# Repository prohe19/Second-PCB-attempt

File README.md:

# Second-PCB-attempt

well here we go my second attempt of creating PCB of mechanical keyboard

I supposed we'll call it a numpad board? well because it only consists of 17 MX only hotswap switches (finally using matrix yeay!!)

this time on my second attempt I tried to include a rotary encoder so that you use to control volume on your pc, scroll up or down and many more!
also I included an 9.1 OLED LCD display why? I believe the right term to desribe it is just for "fun" :D
well you can use the LCD display to display the capslock on or just to display silly small pictures on your numpad board.

This version is still not fixed, might change more in the future because Im still not happy with the componen placements.
Again, my priority is AESTHETIC of the PCB sooo it takes me such a loonnggggggg time to design this.

Pros

-HOTSWAPABLE!!!!!!

-rotary encoder

-OLED LCD display

Cons

-no RGB :(

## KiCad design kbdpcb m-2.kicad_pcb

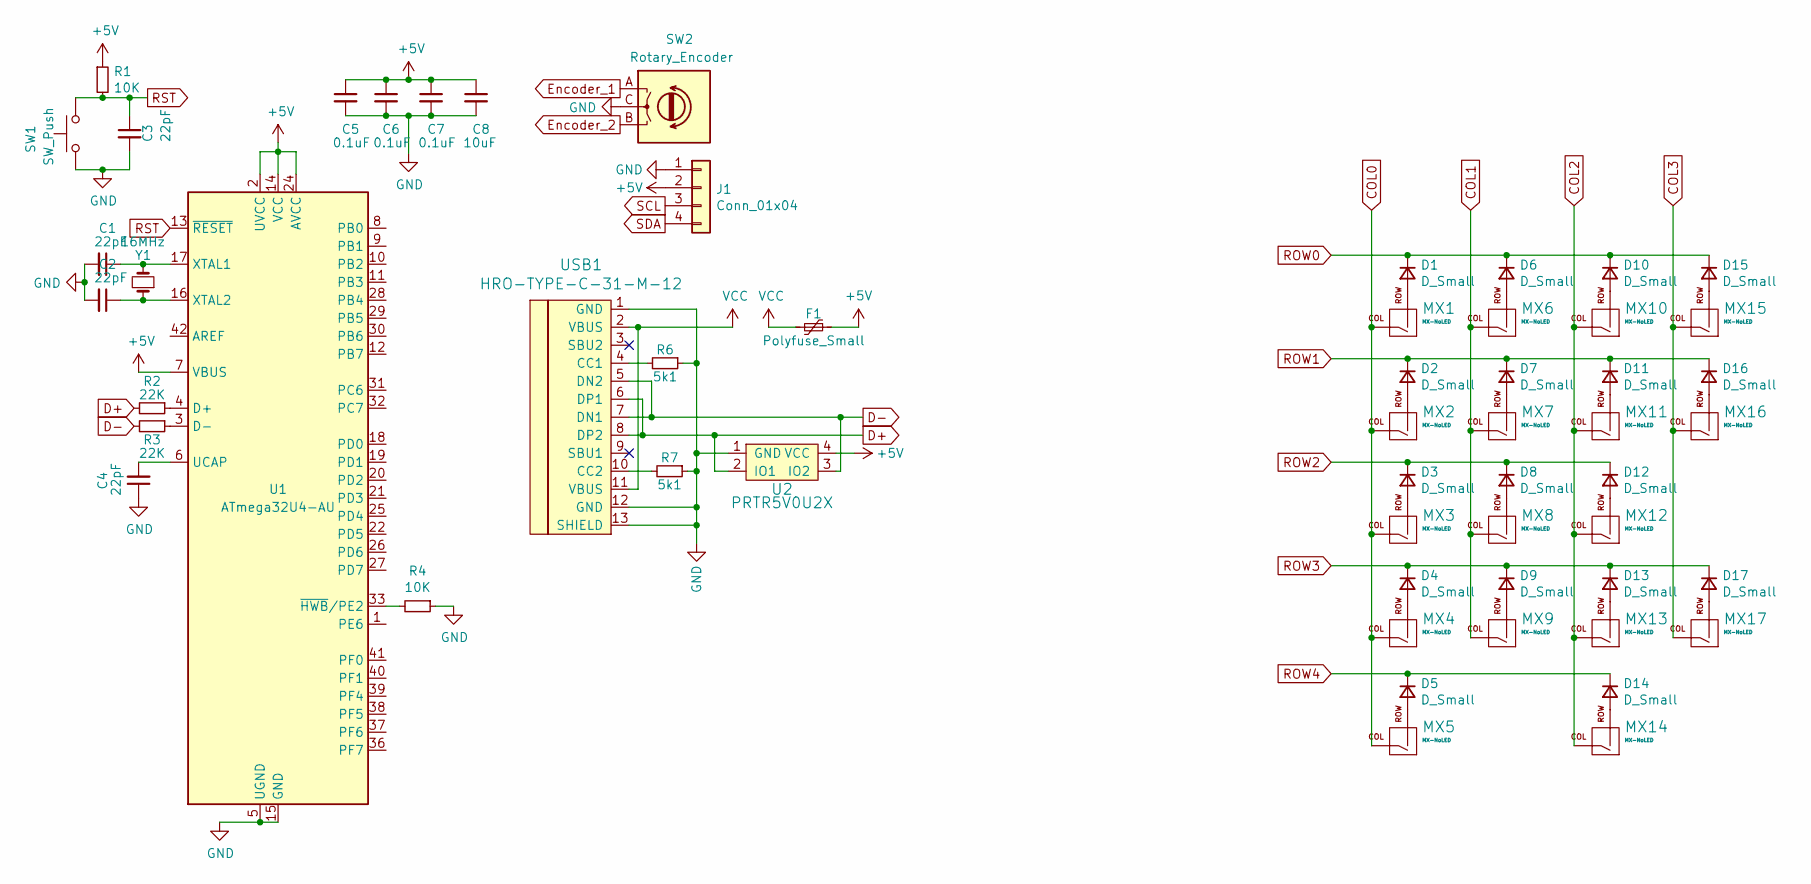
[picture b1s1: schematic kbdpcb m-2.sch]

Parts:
C1, C2, C3, C4: 22pF; C_0805_2012Metric
C5, C6, C7: 0.1uF; C_0805_2012Metric
C8: 10uF; C_0805_2012Metric
D1, D2, D3, D4, D5, D6, D7, D8, D9, D10, D11, D12, D13, D14, D15, D16, D17: D_Small; D_SOD-123
F1: Polyfuse_Small; Fuse_1206_3216Metric
J1: Conn_01x04; Oled_Screen
MX1, MX2, MX3, MX4, MX6, MX7, MX8, MX9, MX10, MX11, MX12, MX13, MX14, MX15: MX-NoLED; MXOnly-1U-Hotswap
MX5, MX16, MX17: MX-NoLED; MXOnly-2U-Hotswap
R1, R4: 10K; R_0805_2012Metric
R2, R3: 22K; R_0805_2012Metric
R6, R7: 5k1; R_0805_2012Metric
SW1: SW_Push; SKQG-1155865
SW2: Rotary_Encoder; RotaryEncoder_Alps_EC11E-Switch_Vertical_H20mm
U1: ATmega32U4-AU; TQFP-44_10x10mm_P0.8mm
U2: PRTR5V0U2X; SOT143B
USB1: HRO-TYPE-C-31-M-12; HRO-TYPE-C-31-M-12-Assembly
Y1: 16MHz; Crystal_SMD_3225-4Pin_3.2x2.5mm

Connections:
+5V: C5.1, C6.1, C7.1, C8.1, F1.1, J1.2, R1.1, U1.2 (UVCC), U1.7 (VBUS), U1.14 (VCC), U1.24 (AVCC), U1.34 (VCC), U1.44 (AVCC), U2.4 (VCC)
COL0: MX1.1 (COL), MX2.1 (COL), MX3.1 (COL), MX4.1 (COL), MX5.1 (COL)
COL1: MX6.1 (COL), MX7.1 (COL), MX8.1 (COL), MX9.1 (COL)
COL2: MX10.1 (COL), MX11.1 (COL), MX12.1 (COL), MX13.1 (COL), MX14.1 (COL)
COL3: MX15.1 (COL), MX16.1 (COL), MX17.1 (COL)
D+: R2.2, U2.2 (IO1), USB1.6 (DP1), USB1.8 (DP2)
D-: R3.2, U2.3 (IO2), USB1.5 (DN2), USB1.7 (DN1)
Encoder_1: SW2.A
Encoder_2: SW2.B
GND: C1.2, C2.2, C3.2, C4.1, C5.2, C6.2, C7.2, C8.2, J1.1, R4.1, R6.1, R7.1, SW1.1, SW2.C, U1.5 (UGND), U1.15 (GND), U1.23 (GND), U1.35 (GND), U1.43 (GND), U2.1 (GND), USB1.1 (GND), USB1.12 (GND), USB1.13 (SHIELD)
unnamed: C1.1, U1.17 (XTAL1), Y1.2
unnamed: C2.1, U1.16 (XTAL2), Y1.1
unnamed: C4.2, U1.6 (UCAP)
unnamed: D1.2 (A), MX1.2 (ROW)
unnamed: D2.2 (A), MX2.2 (ROW)
unnamed: D3.2 (A), MX3.2 (ROW)
unnamed: D4.2 (A), MX4.2 (ROW)
unnamed: D5.2 (A), MX5.2 (ROW)
unnamed: D6.2 (A), MX6.2 (ROW)
unnamed: D7.2 (A), MX7.2 (ROW)
unnamed: D8.2 (A), MX8.2 (ROW)
unnamed: D9.2 (A), MX9.2 (ROW)
unnamed: D10.2 (A), MX10.2 (ROW)
unnamed: D11.2 (A), MX11.2 (ROW)
unnamed: D12.2 (A), MX12.2 (ROW)
unnamed: D13.2 (A), MX13.2 (ROW)
unnamed: D14.2 (A), MX14.2 (ROW)
unnamed: D15.2 (A), MX15.2 (ROW)
unnamed: D16.2 (A), MX16.2 (ROW)
unnamed: D17.2 (A), MX17.2 (ROW)
unnamed: R2.1, U1.4 (D+)
unnamed: R3.1, U1.3 (D-)
unnamed: R4.2, U1.33 (~HWB~/PE2)
unnamed: R6.2, USB1.4 (CC1)
unnamed: R7.2, USB1.10 (CC2)
ROW0: D1.1 (K), D6.1 (K), D10.1 (K), D15.1 (K)
ROW1: D2.1 (K), D7.1 (K), D11.1 (K), D16.1 (K)
ROW2: D3.1 (K), D8.1 (K), D12.1 (K)
ROW3: D4.1 (K), D9.1 (K), D13.1 (K), D17.1 (K)
ROW4: D5.1 (K), D14.1 (K)
RST: C3.1, R1.2, SW1.2, U1.13 (~RESET)
SCL: J1.3
SDA: J1.4
VCC: F1.2, USB1.2 (VBUS), USB1.11 (VBUS)

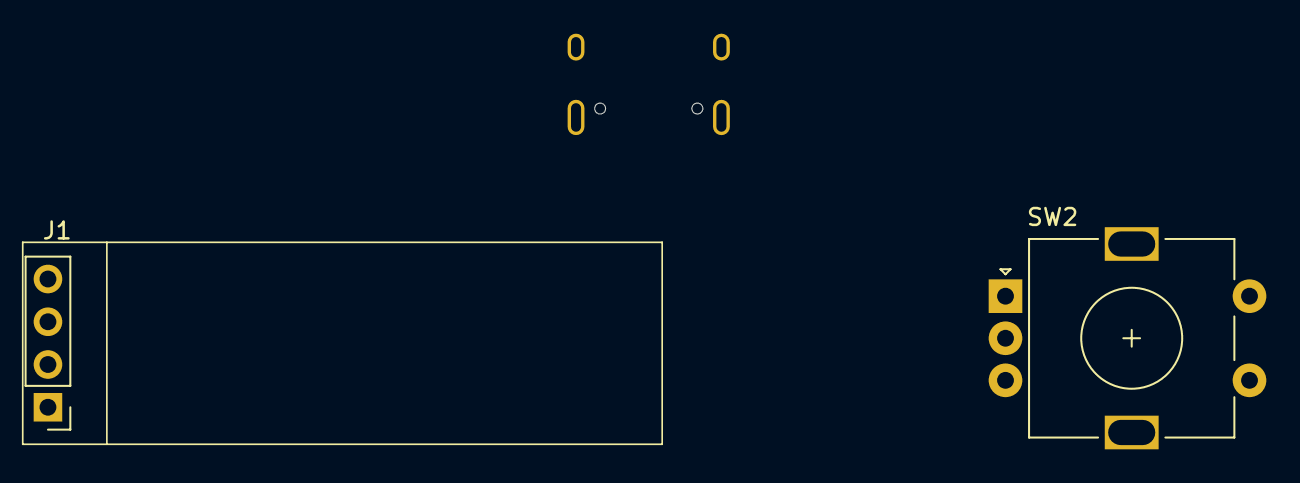
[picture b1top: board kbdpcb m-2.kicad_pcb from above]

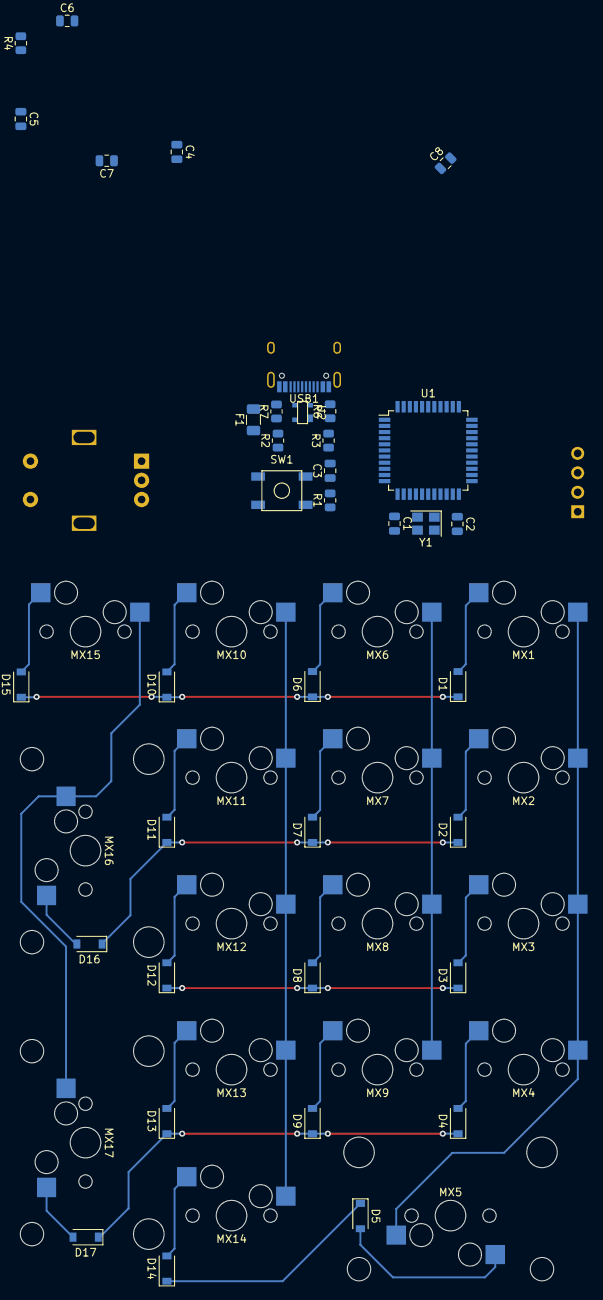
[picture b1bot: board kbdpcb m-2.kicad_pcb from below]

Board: 2 copper layers, 56 parts (37 on the bottom side), 40 nets.
